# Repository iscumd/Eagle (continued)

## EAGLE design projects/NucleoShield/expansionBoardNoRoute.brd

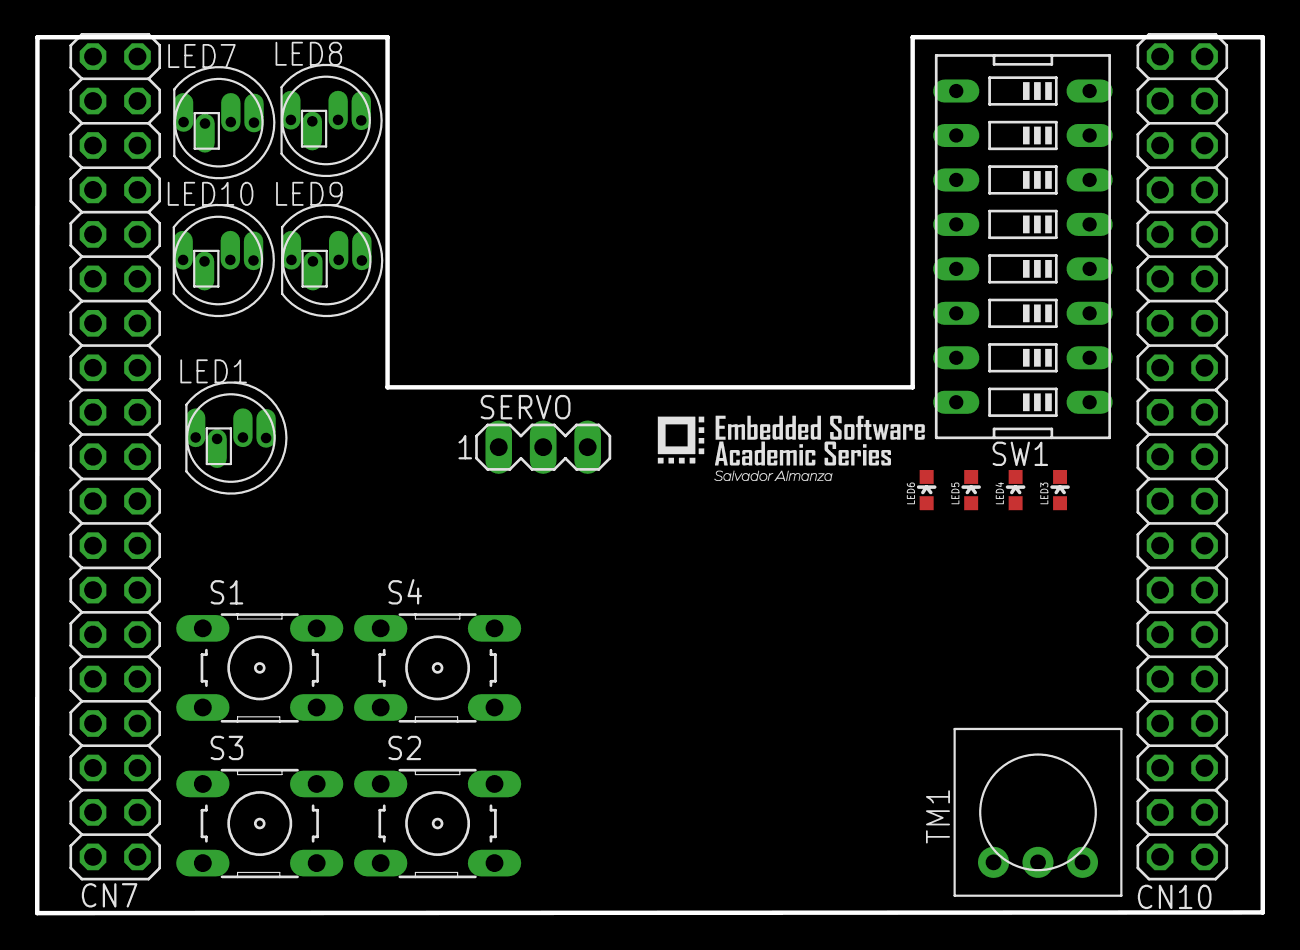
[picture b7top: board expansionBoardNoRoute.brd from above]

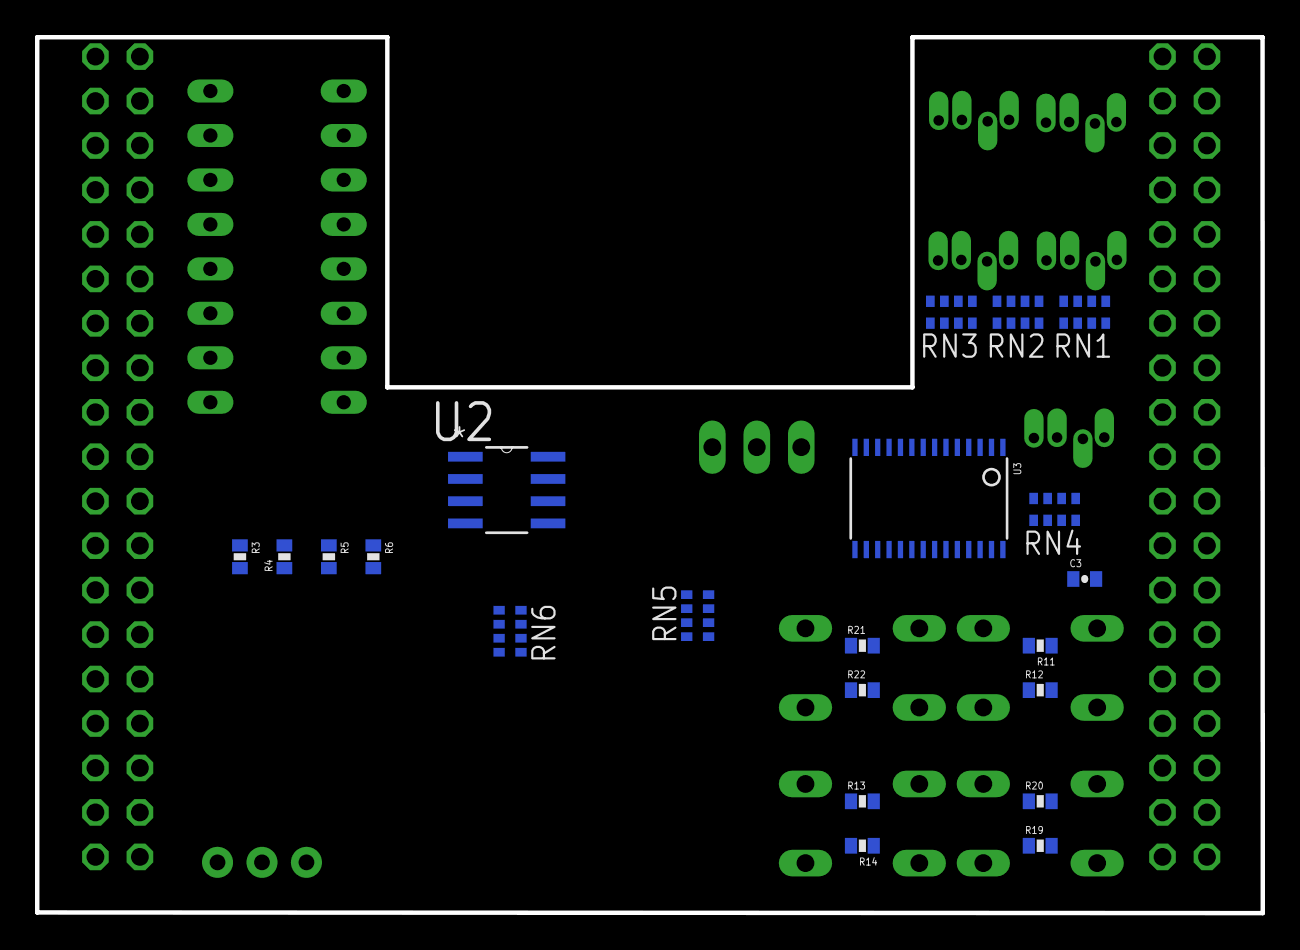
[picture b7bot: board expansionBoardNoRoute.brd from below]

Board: 2 copper layers, 70.0 x 50.0 mm, 39 parts (21 on the bottom side), 61 nets, no tracks yet.

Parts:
C3: 0.1uF; 0402-CAP
CN7, CN10: 2X19
LED1, LED7, LED8, LED9, LED10: RGBLED_CA-5MM; LED5MMRGB
LED3, LED4: Red; LED-0603
LED5, LED6: Green; LED-0603
R3, R4, R5, R6, R12, R14, R20, R22: 470; 0402-RES
R11, R13, R19, R21: 10K; 0402-RES
RN1, RN2, RN3, RN4, RN5, RN6: 0603-ARC
S1, S2, S3, S4: B3F-10XX
SERVO: MA03-1
SW1: EDG-08
TM1: TRIM-3386
U2: 25LC256-I/SNG; SOIC127P600X175-8N
U3: TSSOP28

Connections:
EEPROM_CLK: CN10.11, U2.6
EEPROM_CS: CN10.17, U2.1
EEPROM_MISO: CN10.13, U2.2
EEPROM_MOSI: CN10.15, U2.5
GND: C3.1, CN7.8, CN7.19, CN7.20, CN7.22, CN10.9, CN10.20, LED3.C, LED4.C, R19.1, R21.1, RN6.1, RN6.2, RN6.3, RN6.4, S1.3, S1.4, S2.3, S2.4, SERVO.3, SW1.1, SW1.2, SW1.3, SW1.4, TM1.1, U2.4, U3.1, U3.2, U3.3, U3.4, U3.5, U3.14, U3.23, U3.24
LED3: CN7.1, R3.2
LED4: CN7.3, R4.2
LED5: CN7.13, LED5.C
LED6: CN7.15, LED6.C
unnamed: LED1.1, RN4.8
unnamed: LED1.3, RN4.7
unnamed: LED3.A, R3.1
unnamed: LED4.A, R4.1
unnamed: RN1.1, U3.6
unnamed: RN1.2, U3.7
unnamed: LED5.A, R5.1
unnamed: LED6.A, R6.1
unnamed: RN1.3, U3.8
unnamed: RN1.4, U3.9
unnamed: RN2.1, U3.10
unnamed: RN2.2, U3.11
unnamed: RN2.3, U3.12
unnamed: RN2.4, U3.13
unnamed: RN3.1, U3.15
unnamed: R13.1, R14.2, S2.1
unnamed: R11.1, R12.2, S1.1
unnamed: RN3.2, U3.16
unnamed: RN3.3, U3.17
unnamed: RN3.4, U3.18
unnamed: LED9.1, RN1.8
unnamed: R19.2, R20.2, S3.1
unnamed: R21.2, R22.2, S4.1
unnamed: LED9.3, RN1.7
unnamed: LED9.4, RN1.6
unnamed: LED8.1, RN1.5
unnamed: LED8.3, RN2.8
unnamed: LED8.4, RN2.7
unnamed: LED10.1, RN2.6
unnamed: LED10.3, RN2.5
unnamed: LED10.4, RN3.8
unnamed: LED7.1, RN3.7
unnamed: LED7.3, LED7.4, RN3.6
unnamed: LED1.4, RN4.6
unnamed: RN4.1, U3.19
unnamed: RN4.2, U3.20
unnamed: RN4.3, U3.21
unnamed: RN4.4, U3.22
unnamed: RN4.5, SERVO.1
NC: CN7.9, CN7.10, CN7.11, CN7.26, CN10.10, CN10.36, CN10.38
PA_2: CN10.35, RN6.5, SW1.9
PA_8: CN10.23, RN5.6, SW1.14
PA_9: CN10.21, RN5.7, SW1.15
PA_10: CN10.33, RN6.6, SW1.10
PB_3: CN10.31, RN6.7, SW1.11
PB_4: CN10.27, RN6.8, SW1.12
PB_10: CN10.25, RN5.5, SW1.13
PC_7: CN10.19, RN5.8, SW1.16
POT: CN7.28, TM1.2
SCL: CN10.3, U3.26
SDA: CN10.5, U3.27
VCC: C3.2, LED1.2, LED7.2, LED8.2, LED9.2, LED10.2, R5.2, R6.2, R11.2, R13.2, RN5.1, RN5.2, RN5.3, RN5.4, S3.3, S3.4, S4.3, S4.4, SERVO.2, SW1.5, SW1.6, SW1.7, SW1.8, TM1.3, U2.3, U2.7, U2.8, U3.28

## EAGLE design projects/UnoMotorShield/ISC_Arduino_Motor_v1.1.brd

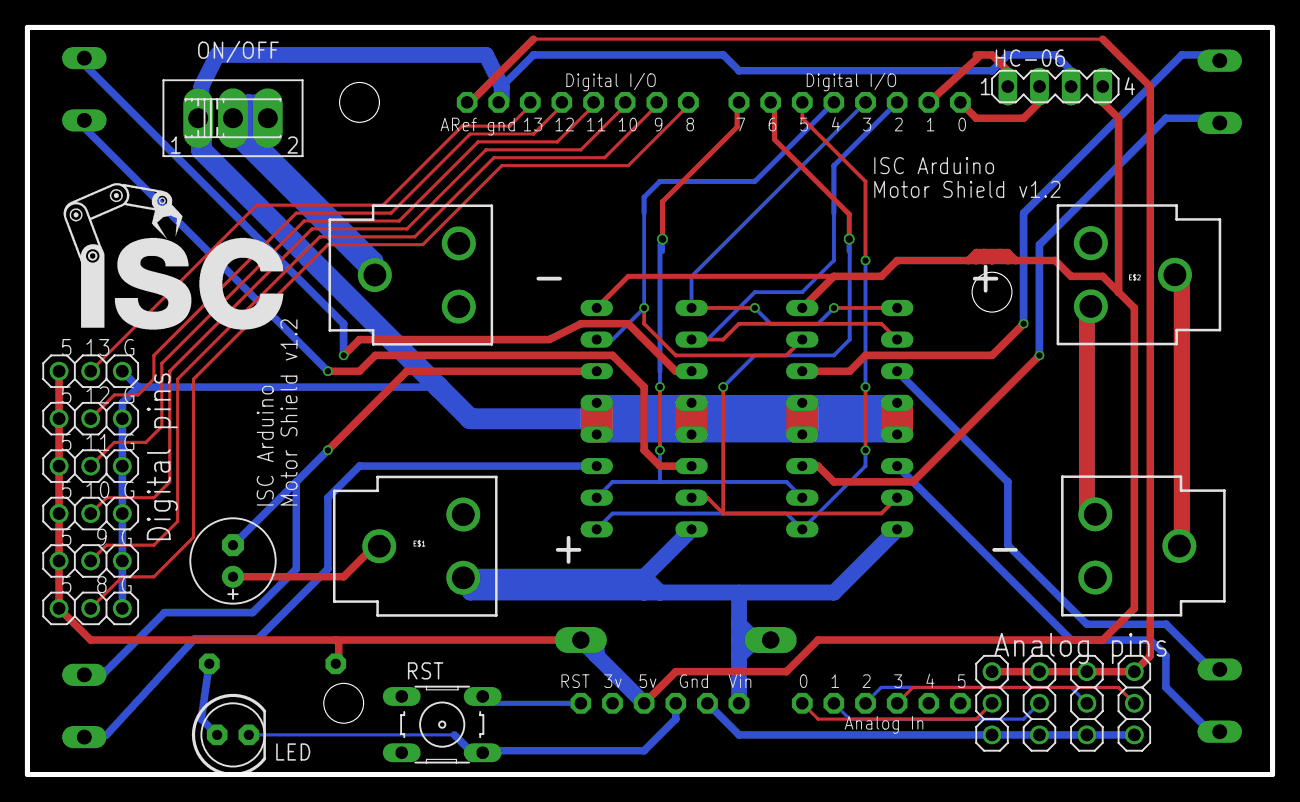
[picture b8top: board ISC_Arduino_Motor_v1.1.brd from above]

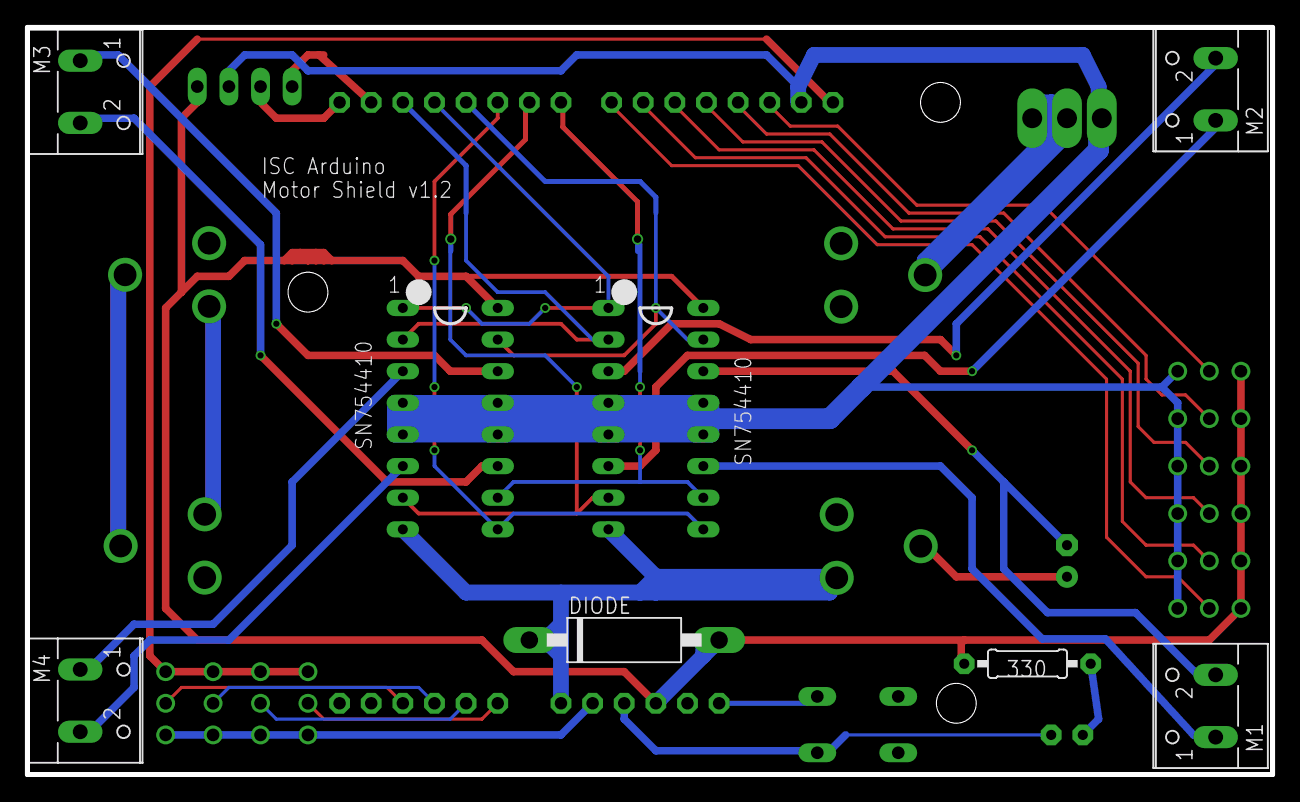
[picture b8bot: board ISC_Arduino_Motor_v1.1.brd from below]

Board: 2 copper layers, 100.0 x 60.0 mm, 26 parts (7 on the bottom side), 17 nets.

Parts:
330: 0207/10
CAP: 100uF; E2,5-7
DIODE: CB417-15
E$1, E$2: BATTERY_18650-HOLDER
E$4: ARDUINO
E$7, E$8: DIP16
E$9, E$11, E$12, E$13, E$16, E$33, E$34, E$35, E$36, E$37: 1X03
HC-06: Rx Tx G Vcc; MA04-1
LED: LED5MM
M1, M2, M3, M4: W237-102
ON/OFF: SLIDE_SWITCH
RST: BUTTON

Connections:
9V: E$4.VIN, E$7.P1, E$8.P16
D1: E$4.D2, E$7.P7, E$8.P10
D2: E$7.P15, E$8.P2
D3: E$4.D4, E$7.P10, E$8.P7
D4: E$7.P2, E$8.P15
GND: E$7.P12, E$8.P5, E$16.3, E$37.3
S1: E$4.D3, E$7.P8, E$8.P9
S2: E$4.D5, E$7.P16, E$8.P1
S$1: E$4.A3, E$9.2
S$3: E$4.GND2, LED.K
S$7: E$4.A2, E$11.2
S$10: CAP.-, E$8.P6
S$11: E$4.A1, E$12.2
S$16: E$4.A0, E$13.2
S$17: E$4.GND1, E$9.1
S$35: 330.2, LED.A
S$54: DIODE.A, E$4.5V, E$7.P9, E$8.P8, E$16.1, E$37.1, HC-06.4
